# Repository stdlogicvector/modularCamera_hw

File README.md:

# ModularCamera Hardware

This repository contains the schematics and layouts for the PCBs that make up the ModularCamera system.
They are divided into three categories:

## Interface

This is the layer that connects the modularCamera to a PC. At the moment the following interfaces are implemented:

- USB3: Using a Cypress FX3 chip to communicate with a PC via an USB-C cable
- GigE: Providing a Gigabit Ethernet connection with an optional PoE add-on board

The boards are fully self contained, bringing all the power supplies and configuration memories they need.
To connect to the next layer, a 70 pin connector transports up to 42 signals plus 22x GND and 6x 5V.

## Processing

The central layer of the stack does everything from controlling the sensors,  processing the data and formatting it for output. Right now, there are two FPGA boards, but microcontrollers would also be possible.

- Spartan7: A XC72S15 FPGA from Xilinx
- Spartan6: A XC6SLX16 FPGA from Xilinx

Besides the FPGA, the boards have several power supplies for the FPGA, a configuration memory and a clock source. The connector to the next layer has  up to 42 signals plus 22x GND and 6x 5V.

## Sensor

This is were the modularity shines. With the high flexibility of the FPGAs, almost all sensors can be interfaced with minimal additional components.
The focus lies on image sensors, but the system isn't limited to processing pixels:

- AISC110C: A small image sensor with a resolution of 80x120 px but a maximum framerate of 40000fps! Configured via SPI.
- ADV7182: An SDTV Video Decoder that accepts lots of analog video formats. Configured via I2C.
- HallArray: An 8x8 array of hall sensors interfaced with an analog matrix. Makes magnetic fields visible.
- MT9P031: A 5MP B/W CMOS image sensor with 14fps. Configured via I2C.
- EV76C560: A 1.3MP B/W CMOS image sensor with global shutter and 60ps. Configured via SPI.
- LinearCCD: A board for interfacing several linear CCD arrays. Provides a driver chip for clocking&control signals, a step-up for power supply and up to 3 12bit 5MSPS ADCs. The sensors are connected via an additional board to accomodate for different pinouts.
- NOIP1SN300: A 1.3MP B/W CMOS image sensor with global shutter and up to 815fps. Configured via SPI.
- IBIS5-B-1300: A 1.3MP B/W CMOS image sensor with global shutter and 27fps. Configured via SPI. (WIP)
- Cameralink: A CameraLink-Base Interface with optional PoCL. Makes the modularCamera into a CameraLink framegrabber. (WIP)
- Microphone Array: A board containing three I2S MEMS microphones. (WIP)

The boards should provide everything necessary to operate the sensor. The connector to the lower layer provides 5V and the control/data interface.

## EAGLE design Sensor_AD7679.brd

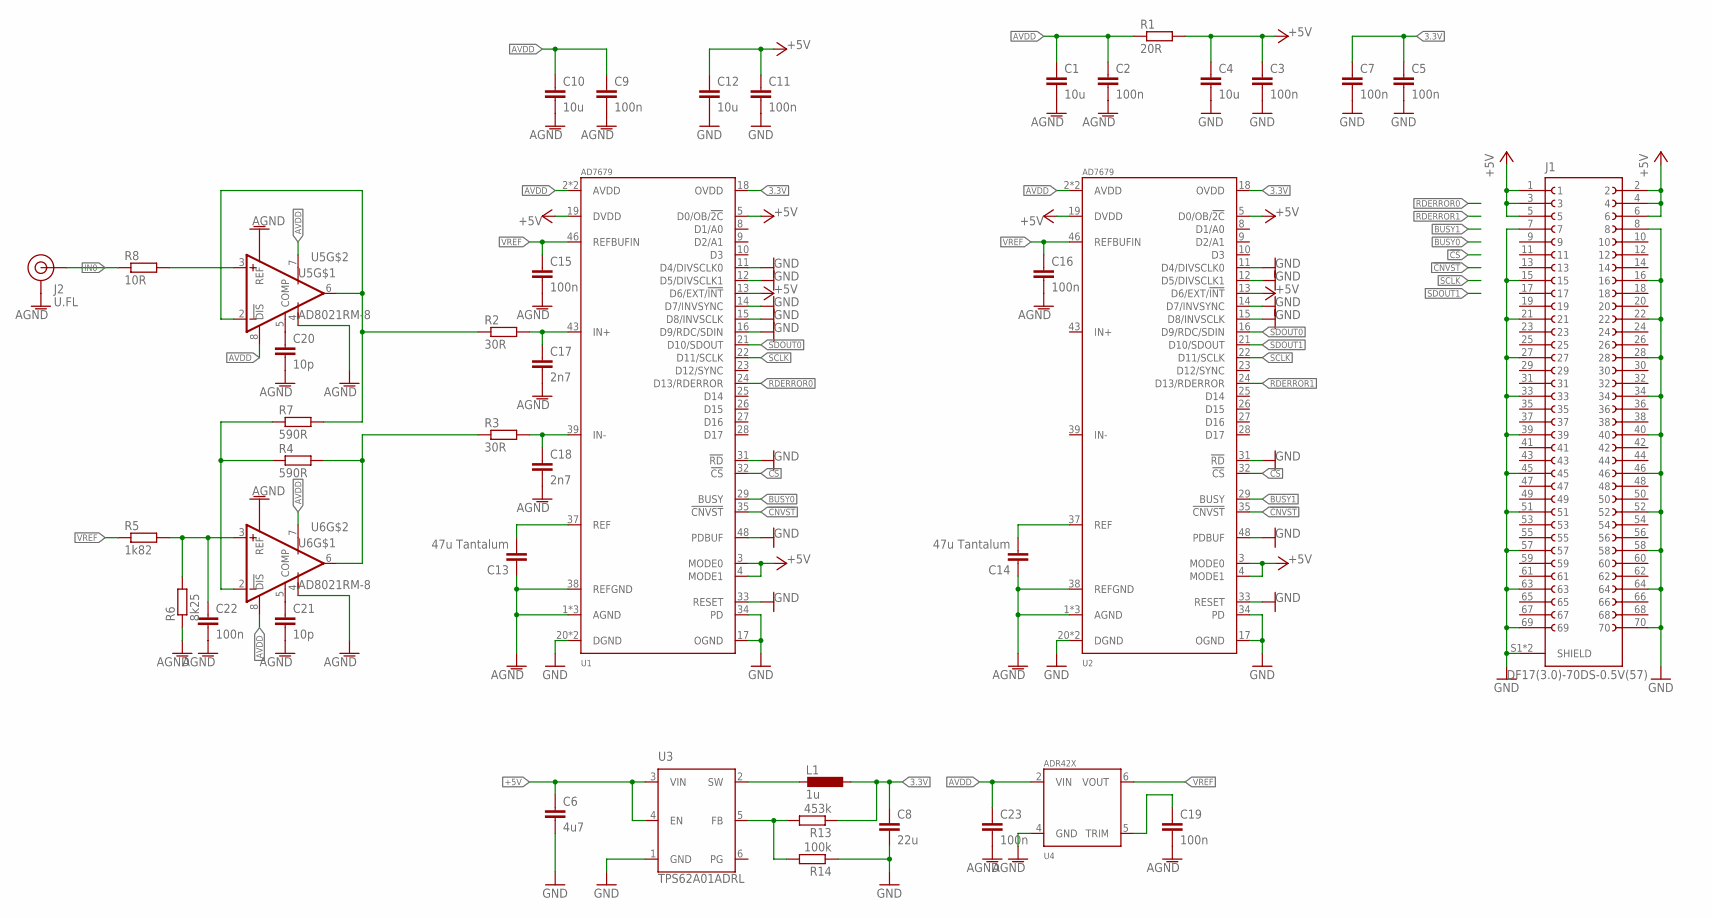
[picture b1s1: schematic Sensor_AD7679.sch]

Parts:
C1, C4, C10, C12: 10u; C0603
C2, C3, C5, C7, C9, C11, C15, C16, C19, C22, C23: 100n; C0402; LCSC C1525
C6: 4u7; C0603; LCSC C19666
C8: 22u; C0603; LCSC C109448
C13, C14: 47u Tantalum; C1206; DIGIKEY 478-TCA0J476M8R-02CT-ND
C17, C18: 2n7; C0402
C20, C21: 10p; C0402
J1: DF17(3.0)-70DS-0.5V(57)
J2: U.FL; DIGIKEY 26-U.FL-R-SMT-1(01)-ND
L1: 1u; L1008; MPN LQM2HPN1R0MG0L; DIGIKEY 490-5112-1-ND
R1: 20R; R0402
R2, R3: 30R; R0402
R4, R7: 590R; R0402
R5: 1k82; R0402
R6: 8k25; R0402
R8: 10R; R0402
R13: 453k; R0402; LCSC C137978
R14: 100k; R0402; DIGIKEY RMCF0402FT100KCT-ND
U1, U2: AD7679; LQFP48
U3: TPS62A01ADRL; SOTFL50P160X60-6N; DIGIKEY 296-TPS62A01ADRLRCT-ND
U4: ADR42X; MSOP08
U5, U6: AD8021RM-8; MSOP08

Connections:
3.3V: C5.1, C7.1, C8.1, L1.1, R13.1, U1.18 (OVDD), U2.18 (OVDD)
!CNVST: U1.35 (!CNVST), U2.35 (!CNVST)
!CS: U1.32 (!CS), U2.32 (!CS)
+5V: C3.1, C4.1, C6.1, C11.1, C12.1, J1.1, J1.2, J1.3, J1.4, J1.5, J1.6, R1.2, U1.3 (MODE0), U1.4 (MODE1), U1.5 (D0/OB/!2C), U1.19 (DVDD), U2.3 (MODE0), U2.4 (MODE1), U2.5 (D0/OB/!2C), U2.13 (D6/EXT/!INT), U2.19 (DVDD), U3.3 (VIN), U3.4 (EN)
AGND: C1.2, C2.2, C9.2, C10.2, C13.1, C14.1, C15.2, C16.2, C17.2, C18.2, C19.2, C20.2, C21.2, C22.2, C23.2, J2.1 (GND), J2.2 (GND), R6.1, U1.1 (AGND), U1.36 (AGND), U1.38 (REFGND), U1.44 (AGND), U2.1 (AGND), U2.36 (AGND), U2.38 (REFGND), U2.44 (AGND), U4.4 (GND), U5.1 (REF), U5.4 (V-), U6.1 (REF), U6.4 (V-)
AVDD: C1.1, C2.1, C9.1, C10.1, C23.1, R1.1, U1.2 (AVDD), U1.47 (AVDD), U2.2 (AVDD), U2.47 (AVDD), U4.2 (VIN), U5.7 (V+), U5.8 (!DIS), U6.7 (V+), U6.8 (!DIS)
BUSY0: U1.29 (BUSY)
BUSY1: U2.29 (BUSY)
GND: C3.2, C4.2, C5.2, C6.2, C7.2, C8.2, C11.2, C12.2, J1.7, J1.8, J1.15, J1.16, J1.21, J1.22, J1.27, J1.28, J1.33, J1.34, J1.39, J1.40, J1.45, J1.46, J1.51, J1.52, J1.57, J1.58, J1.63, J1.64, J1.69, J1.70, J1.S1 (SHIELD), J1.S2 (SHIELD), R14.1, U1.11 (D4/DIVSCLK0), U1.12 (D5/DIVSCLK1), U1.14 (D7/INVSYNC), U1.17 (OGND), U1.20 (DGND), U1.30 (DGND), U1.31 (!RD), U1.33 (RESET), U1.34 (PD), U1.48 (PDBUF), U2.11 (D4/DIVSCLK0), U2.12 (D5/DIVSCLK1), U2.14 (D7/INVSYNC), U2.15 (D8/INVSCLK), U2.17 (OGND), U2.20 (DGND), U2.30 (DGND), U2.31 (!RD), U2.33 (RESET), U2.34 (PD), U2.48 (PDBUF), U3.1 (GND)
IN0: J2.FEED (SIGNAL), R8.1
unnamed: C13.2, U1.37 (REF)
unnamed: C14.2, U2.37 (REF)
unnamed: U1.15 (D8/INVSCLK), U1.16 (D9/RDC/SDIN)
unnamed: R2.1, R7.2, U5.2 (-IN), U5.6 (OUT)
unnamed: C20.1, U5.5 (COMP)
unnamed: C17.1, R2.2, U1.43 (IN+)
unnamed: C18.1, R3.2, U1.39 (IN-)
unnamed: C19.1, U4.5 (TRIM)
unnamed: R4.1, R7.1, U6.2 (-IN)
unnamed: C21.1, U6.5 (COMP)
unnamed: R3.1, R4.2, U6.6 (OUT)
unnamed: C22.1, R5.2, R6.2, U6.3 (+IN)
unnamed: R8.2, U5.3 (+IN)
unnamed: R13.2, R14.2, U3.5 (FB)
unnamed: L1.2, U3.2 (SW)
RDERROR0: U1.24 (D13/RDERROR)
RDERROR1: U2.24 (D13/RDERROR)
SCLK: U1.22 (D11/SCLK), U2.22 (D11/SCLK)
SDOUT0: U1.21 (D10/SDOUT), U2.16 (D9/RDC/SDIN)
SDOUT1: U2.21 (D10/SDOUT)
VREF: C15.1, C16.1, R5.1, U1.46 (REFBUFIN), U2.46 (REFBUFIN), U4.6 (VOUT)

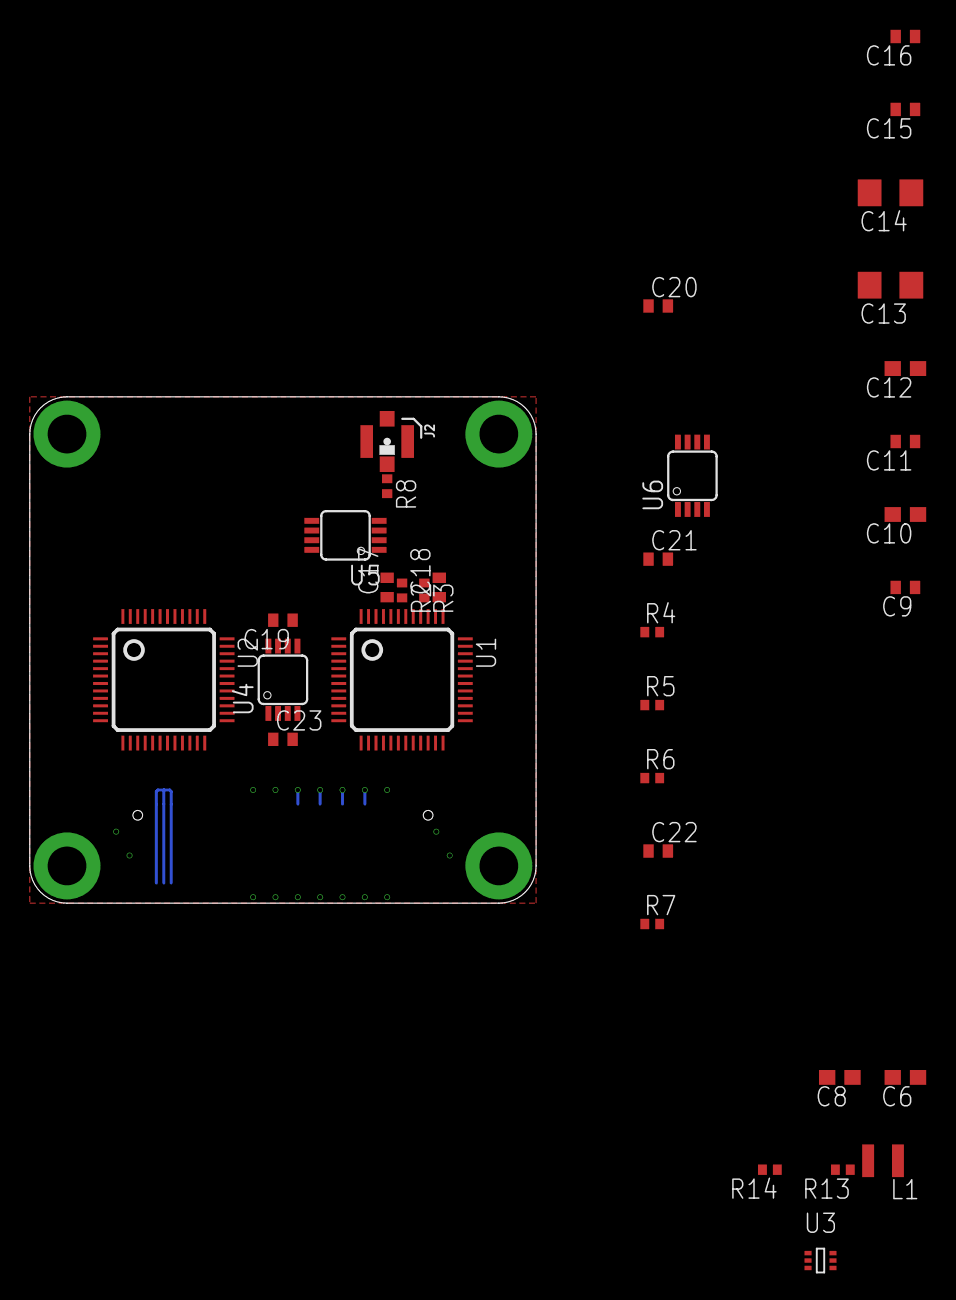
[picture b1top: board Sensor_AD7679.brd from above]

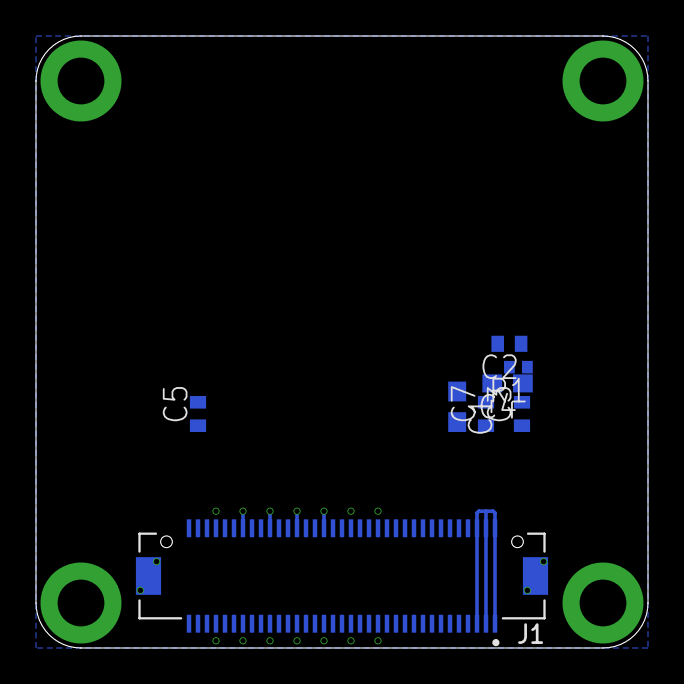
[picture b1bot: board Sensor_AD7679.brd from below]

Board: 4 copper layers, 34.0 x 34.0 mm, 42 parts (8 on the bottom side), 26 nets.

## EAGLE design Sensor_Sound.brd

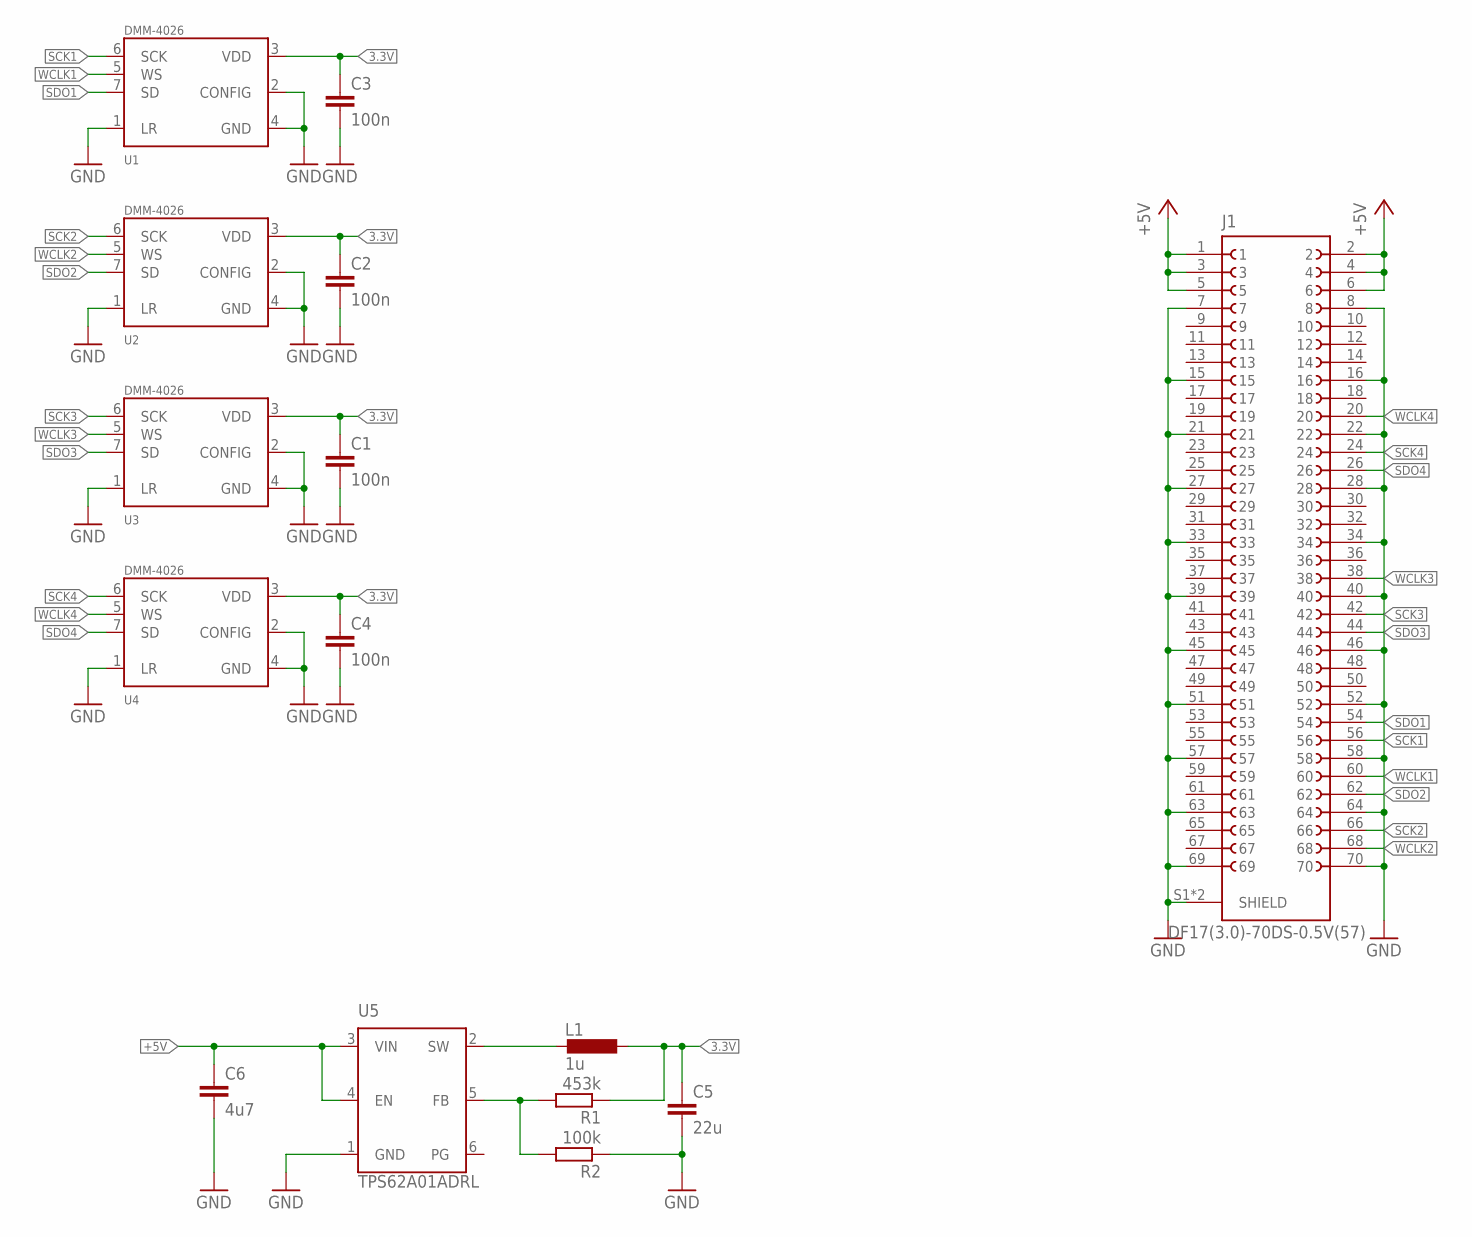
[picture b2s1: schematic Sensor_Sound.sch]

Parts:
C1, C2, C3, C4: 100n; C0402; LCSC C1525
C5: 22u; C0603; LCSC C109448
C6: 4u7; C0603; LCSC C19666
J1: DF17(3.0)-70DS-0.5V(57)
L1: 1u; L1008; MPN LQM2HPN1R0MG0L; DIGIKEY 490-5112-1-ND
R1: 453k; R0402; LCSC C137978
R2: 100k; R0402; DIGIKEY RMCF0402FT100KCT-ND
U1, U2, U3, U4: DMM-4026
U5: TPS62A01ADRL; SOTFL50P160X60-6N; DIGIKEY 296-TPS62A01ADRLRCT-ND

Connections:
3.3V: C1.1, C2.1, C3.1, C4.1, C5.1, L1.1, R1.1, U1.3 (VDD), U2.3 (VDD), U3.3 (VDD), U4.3 (VDD)
+5V: C6.1, J1.1, J1.2, J1.3, J1.4, J1.5, J1.6, U5.3 (VIN), U5.4 (EN)
GND: C1.2, C2.2, C3.2, C4.2, C5.2, C6.2, J1.7, J1.8, J1.15, J1.16, J1.21, J1.22, J1.27, J1.28, J1.33, J1.34, J1.39, J1.40, J1.45, J1.46, J1.51, J1.52, J1.57, J1.58, J1.63, J1.64, J1.69, J1.70, J1.S1 (SHIELD), J1.S2 (SHIELD), R2.1, U1.1 (LR), U1.2 (CONFIG), U1.4 (GND), U2.1 (LR), U2.2 (CONFIG), U2.4 (GND), U3.1 (LR), U3.2 (CONFIG), U3.4 (GND), U4.1 (LR), U4.2 (CONFIG), U4.4 (GND), U5.1 (GND)
unnamed: R1.2, R2.2, U5.5 (FB)
unnamed: L1.2, U5.2 (SW)
SCK1: J1.56, U1.6 (SCK)
SCK2: J1.66, U2.6 (SCK)
SCK3: J1.42, U3.6 (SCK)
SCK4: J1.24, U4.6 (SCK)
SDO1: J1.54, U1.7 (SD)
SDO2: J1.62, U2.7 (SD)
SDO3: J1.44, U3.7 (SD)
SDO4: J1.26, U4.7 (SD)
WCLK1: J1.60, U1.5 (WS)
WCLK2: J1.68, U2.5 (WS)
WCLK3: J1.38, U3.5 (WS)
WCLK4: J1.20, U4.5 (WS)

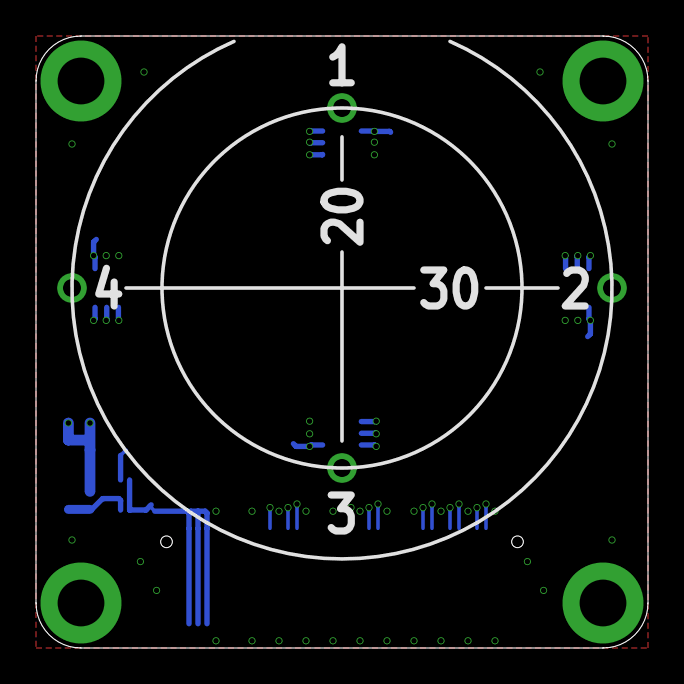
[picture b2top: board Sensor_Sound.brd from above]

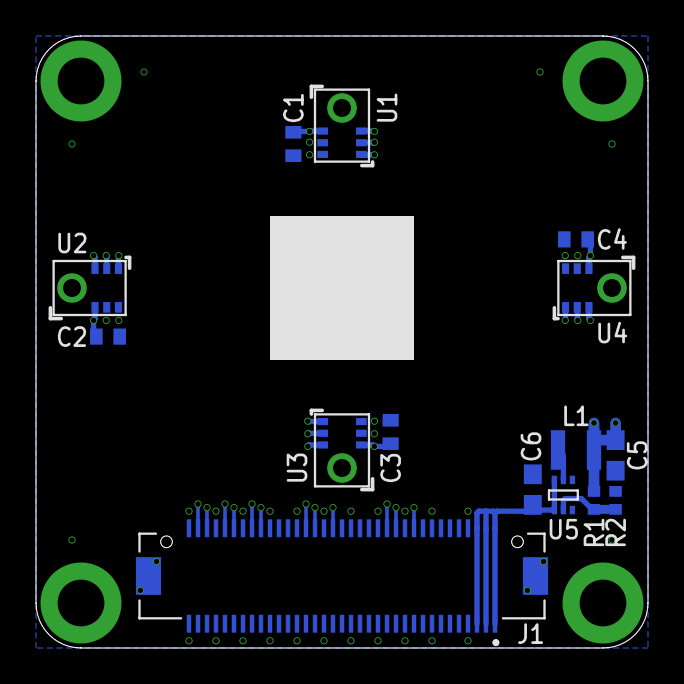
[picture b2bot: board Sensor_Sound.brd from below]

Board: 4 copper layers, 34.0 x 34.0 mm, 15 parts (15 on the bottom side), 17 nets.

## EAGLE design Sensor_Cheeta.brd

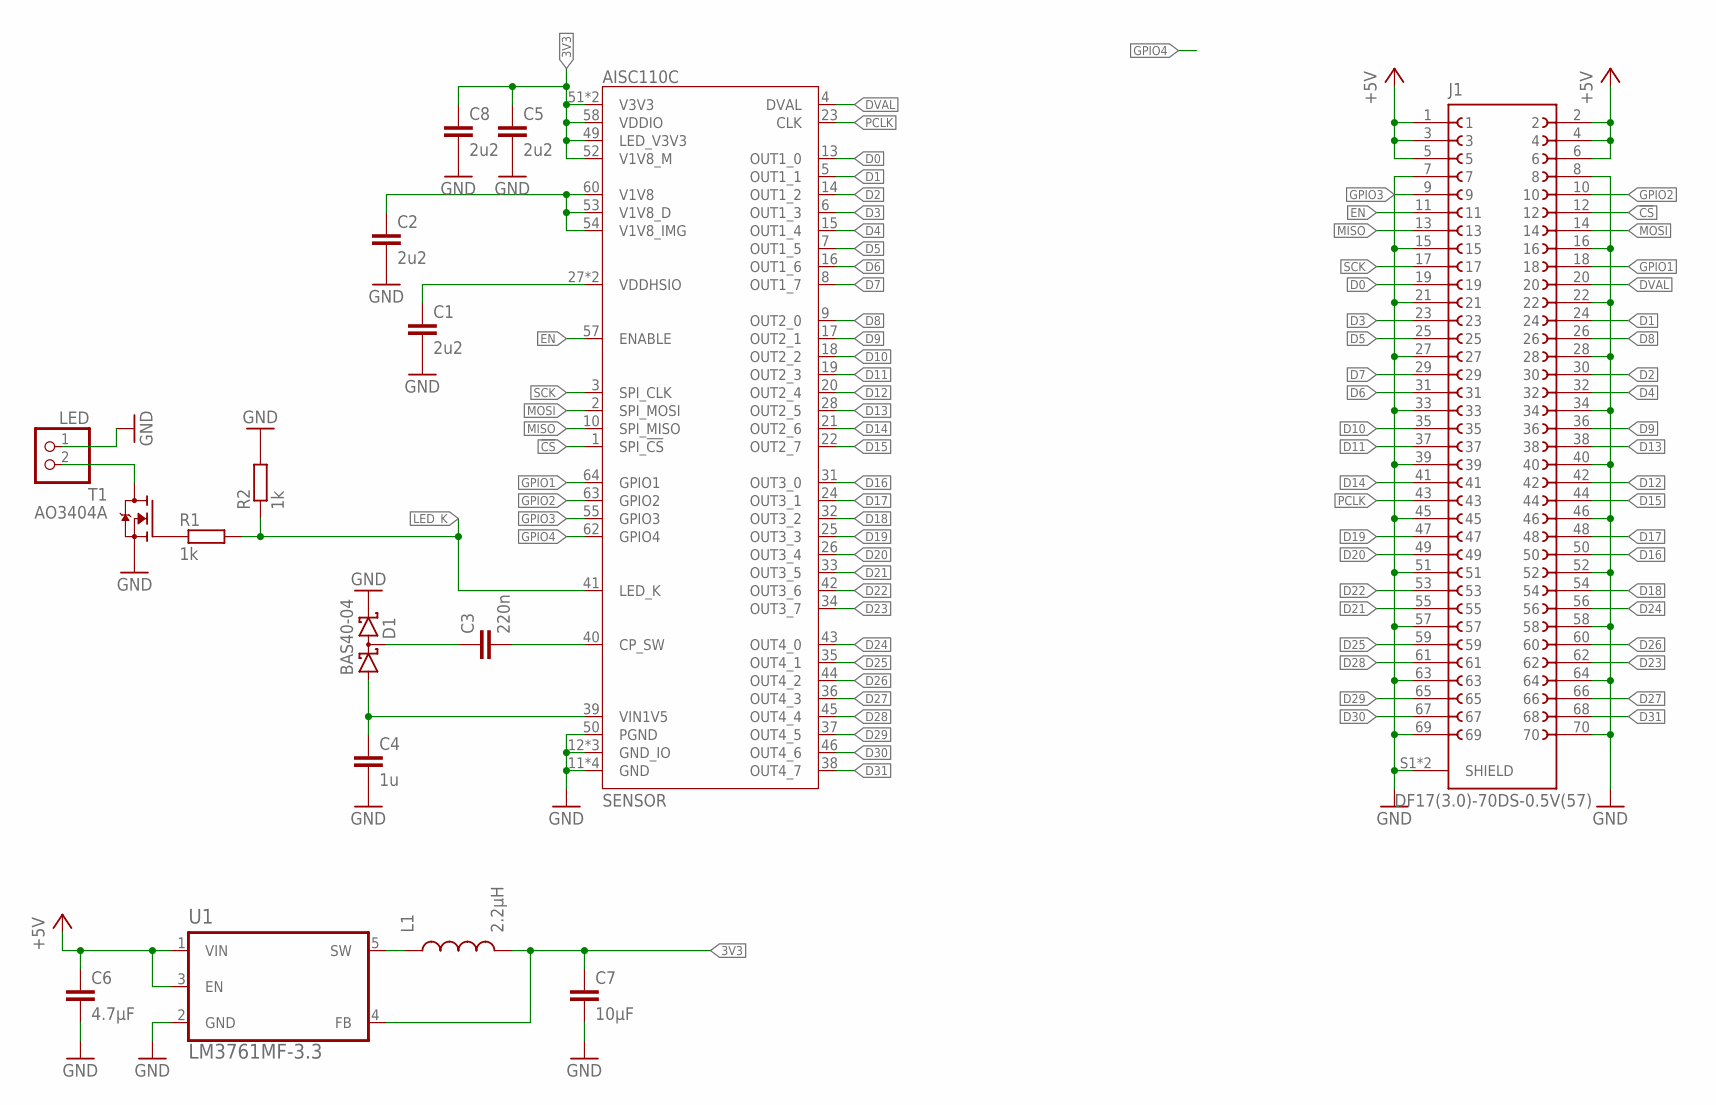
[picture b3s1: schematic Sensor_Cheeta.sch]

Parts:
C1, C2, C5, C8: 2u2; C0603
C3: 220n; C0603
C4: 1u; C0603
C6: 4.7µF; C0603
C7: 10µF; C0603
D1: BAS40-04; SOT23
J1: DF17(3.0)-70DS-0.5V(57)
L1: 2.2µH; SO3314; FARNELL 2457514
LED: PINHD-1X2; 1X02
R1, R2: 1k; R0603; LCSC C11702
SENSOR: AISC110C; 64_LD_OLGA
T1: AO3404A; SOT23; LCSC C30010
U1: LM3761MF-3.3; SOT95P284X122-5N

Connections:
3V3: C5.1, C7.1, C8.1, L1.2, SENSOR.49 (LED_V3V3), SENSOR.51 (V3V3), SENSOR.52 (V1V8_M), SENSOR.58 (VDDIO), SENSOR.59 (V3V3), U1.4 (FB)
!CS: J1.12, SENSOR.1 (SPI_!CS)
+5V: C6.1, J1.1, J1.2, J1.3, J1.4, J1.5, J1.6, U1.1 (VIN), U1.3 (EN)
D0: J1.19, SENSOR.13 (OUT1_0)
D1: J1.24, SENSOR.5 (OUT1_1)
D2: J1.30, SENSOR.14 (OUT1_2)
D3: J1.23, SENSOR.6 (OUT1_3)
D4: J1.32, SENSOR.15 (OUT1_4)
D5: J1.25, SENSOR.7 (OUT1_5)
D6: J1.31, SENSOR.16 (OUT1_6)
D7: J1.29, SENSOR.8 (OUT1_7)
D8: J1.26, SENSOR.9 (OUT2_0)
D9: J1.36, SENSOR.17 (OUT2_1)
D10: J1.35, SENSOR.18 (OUT2_2)
D11: J1.37, SENSOR.19 (OUT2_3)
D12: J1.42, SENSOR.20 (OUT2_4)
D13: J1.38, SENSOR.28 (OUT2_5)
D14: J1.41, SENSOR.21 (OUT2_6)
D15: J1.44, SENSOR.22 (OUT2_7)
D16: J1.50, SENSOR.31 (OUT3_0)
D17: J1.48, SENSOR.24 (OUT3_1)
D18: J1.54, SENSOR.32 (OUT3_2)
D19: J1.47, SENSOR.25 (OUT3_3)
D20: J1.49, SENSOR.26 (OUT3_4)
D21: J1.55, SENSOR.33 (OUT3_5)
D22: J1.53, SENSOR.42 (OUT3_6)
D23: J1.62, SENSOR.34 (OUT3_7)
D24: J1.56, SENSOR.43 (OUT4_0)
D25: J1.59, SENSOR.35 (OUT4_1)
D26: J1.60, SENSOR.44 (OUT4_2)
D27: J1.66, SENSOR.36 (OUT4_3)
D28: J1.61, SENSOR.45 (OUT4_4)
D29: J1.65, SENSOR.37 (OUT4_5)
D30: J1.67, SENSOR.46 (OUT4_6)
D31: J1.68, SENSOR.38 (OUT4_7)
DVAL: J1.20, SENSOR.4 (DVAL)
EN: J1.11, SENSOR.57 (ENABLE)
GND: C1.2, C2.2, C4.2, C5.2, C6.2, C7.2, C8.2, D1.2 (C2), J1.7, J1.8, J1.15, J1.16, J1.21, J1.22, J1.27, J1.28, J1.33, J1.34, J1.39, J1.40, J1.45, J1.46, J1.51, J1.52, J1.57, J1.58, J1.63, J1.64, J1.69, J1.70, J1.S1 (SHIELD), J1.S2 (SHIELD), LED.1, R2.2, SENSOR.11 (GND), SENSOR.12 (GND_IO), SENSOR.30 (GND_IO), SENSOR.47 (GND_IO), SENSOR.48 (GND), SENSOR.50 (PGND), SENSOR.56 (GND), SENSOR.61 (GND), T1.2 (S), U1.2 (GND)
GPIO1: J1.18, SENSOR.64 (GPIO1)
GPIO2: J1.10, SENSOR.63 (GPIO2)
GPIO3: J1.9, SENSOR.55 (GPIO3)
GPIO4: SENSOR.62 (GPIO4)
LED_K: R1.2, R2.1, SENSOR.41 (LED_K)
MISO: J1.13, SENSOR.10 (SPI_MISO)
MOSI: J1.14, SENSOR.2 (SPI_MOSI)
unnamed: C3.2, SENSOR.40 (CP_SW)
unnamed: C4.1, D1.1 (A1), SENSOR.39 (VIN1V5)
unnamed: C3.1, D1.3 (C1A2)
unnamed: LED.2, T1.3 (D)
unnamed: L1.1, U1.5 (SW)
unnamed: C2.1, SENSOR.53 (V1V8_D), SENSOR.54 (V1V8_IMG), SENSOR.60 (V1V8)
unnamed: C1.1, SENSOR.27 (VDDHSIO), SENSOR.29 (VDDHSIO)
unnamed: R1.1, T1.1 (G)
PCLK: J1.43, SENSOR.23 (CLK)
SCK: J1.17, SENSOR.3 (SPI_CLK)

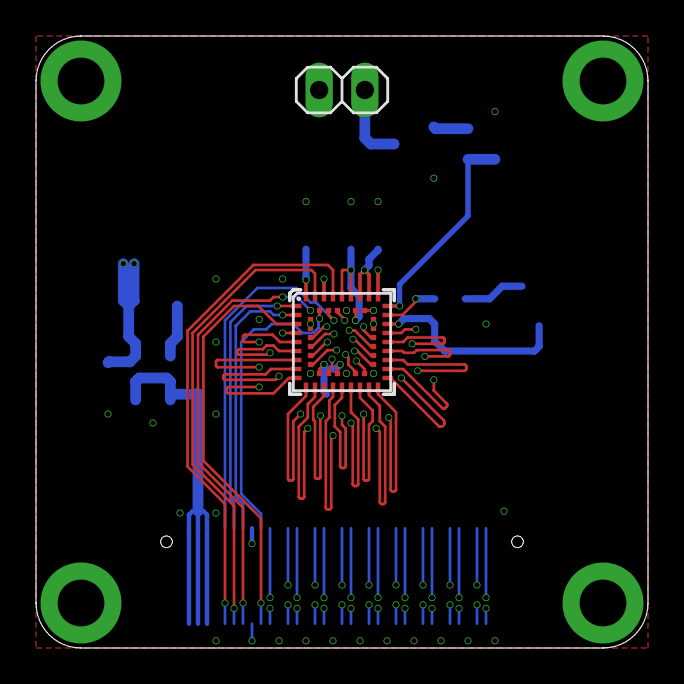
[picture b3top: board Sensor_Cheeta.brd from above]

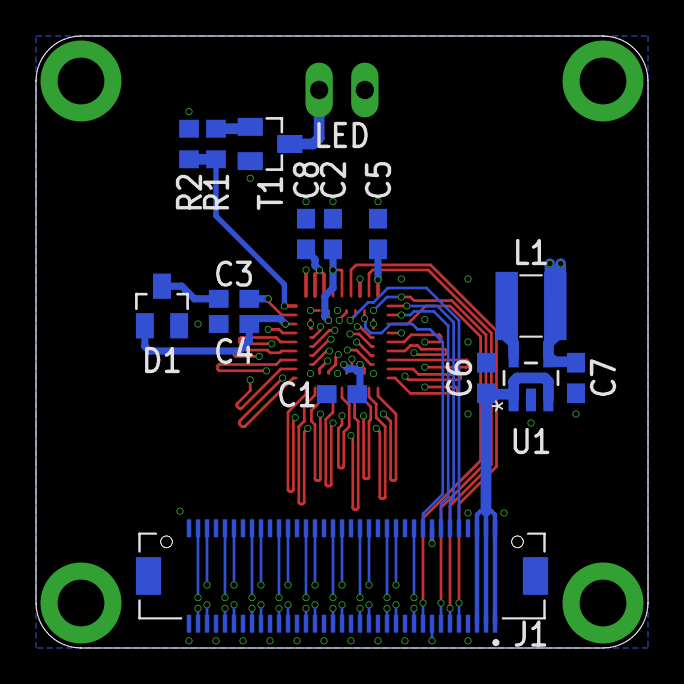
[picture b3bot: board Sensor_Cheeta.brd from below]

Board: 4 copper layers, 34.0 x 34.0 mm, 17 parts (15 on the bottom side), 54 nets.

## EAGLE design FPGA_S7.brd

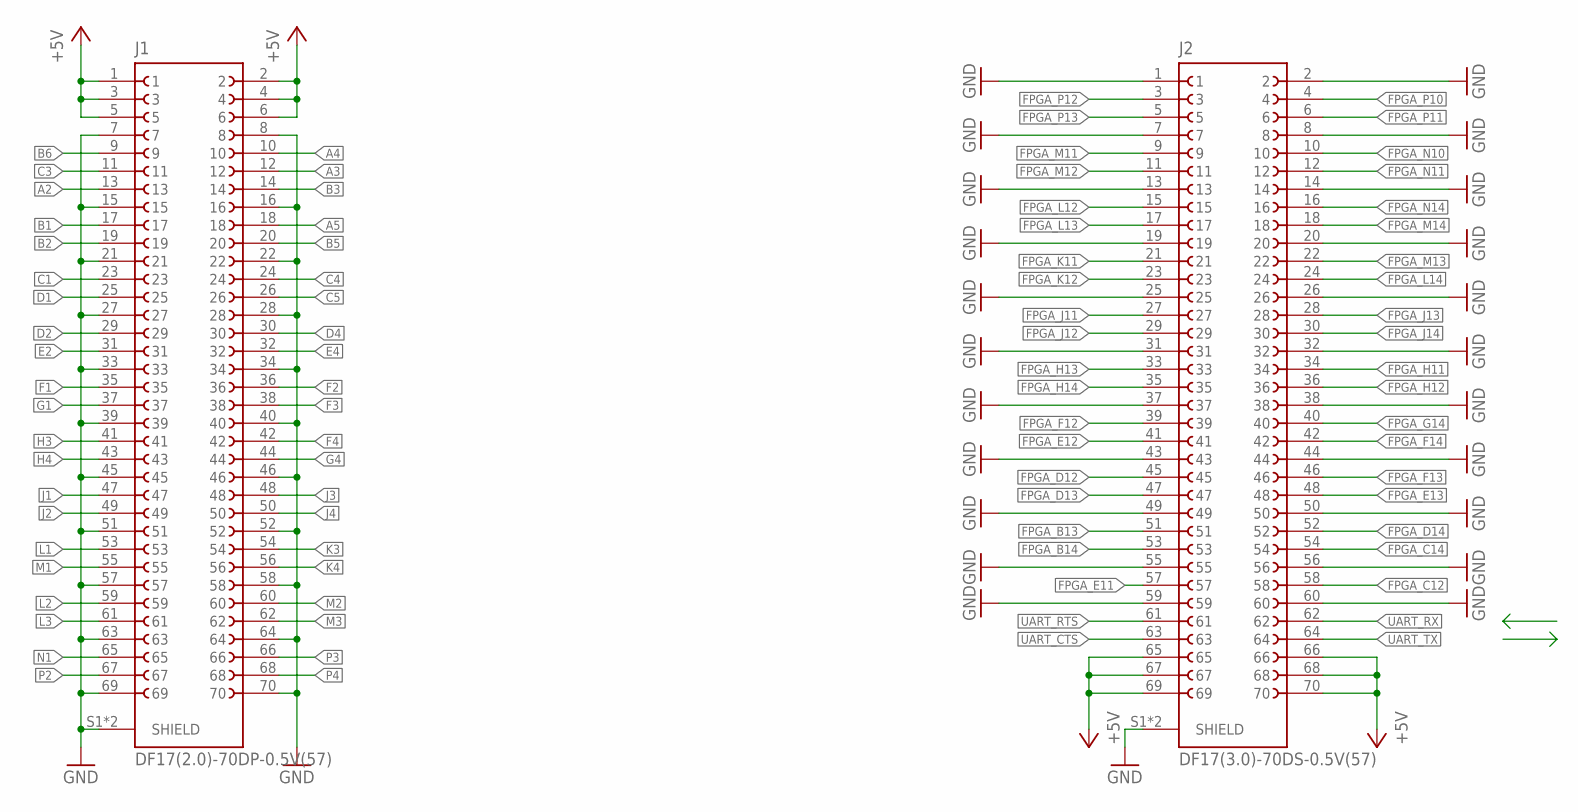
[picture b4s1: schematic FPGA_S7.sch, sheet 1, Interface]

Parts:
J1: DF17(2.0)-70DP-0.5V(57); DIGIKEY H11133CT-ND
J2: DF17(3.0)-70DS-0.5V(57); DIGIKEY H11112CT-ND

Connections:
+5V: J1.1, J1.2, J1.3, J1.4, J1.5, J1.6, J2.65, J2.66, J2.67, J2.68, J2.69, J2.70; also elsewhere on the board
A2: J1.13; also elsewhere on the board
A3: J1.12; also elsewhere on the board
A4: J1.10; also elsewhere on the board
A5: J1.18; also elsewhere on the board
B1: J1.17; also elsewhere on the board
B2: J1.19; also elsewhere on the board
B3: J1.14; also elsewhere on the board
B5: J1.20; also elsewhere on the board
B6: J1.9; also elsewhere on the board
C1: J1.23; also elsewhere on the board
C3: J1.11; also elsewhere on the board
C4: J1.24; also elsewhere on the board
C5: J1.26; also elsewhere on the board
D1: J1.25; also elsewhere on the board
D2: J1.29; also elsewhere on the board
D4: J1.30; also elsewhere on the board
E2: J1.31; also elsewhere on the board
E4: J1.32; also elsewhere on the board
F1: J1.35; also elsewhere on the board
F2: J1.36; also elsewhere on the board
F3: J1.38; also elsewhere on the board
F4: J1.42; also elsewhere on the board
FPGA_B13: J2.51; also elsewhere on the board
FPGA_B14: J2.53; also elsewhere on the board
FPGA_C12: J2.58; also elsewhere on the board
FPGA_C14: J2.54; also elsewhere on the board
FPGA_D12: J2.45; also elsewhere on the board
FPGA_D13: J2.47; also elsewhere on the board
FPGA_D14: J2.52; also elsewhere on the board
FPGA_E11: J2.57; also elsewhere on the board
FPGA_E12: J2.41; also elsewhere on the board
FPGA_E13: J2.48; also elsewhere on the board
FPGA_F12: J2.39; also elsewhere on the board
FPGA_F13: J2.46; also elsewhere on the board
FPGA_F14: J2.42; also elsewhere on the board
FPGA_G14: J2.40; also elsewhere on the board
FPGA_H11: J2.34; also elsewhere on the board
FPGA_H12: J2.36; also elsewhere on the board
FPGA_H13: J2.33; also elsewhere on the board
FPGA_H14: J2.35; also elsewhere on the board
FPGA_J11: J2.27; also elsewhere on the board
FPGA_J12: J2.29; also elsewhere on the board
FPGA_J13: J2.28; also elsewhere on the board
FPGA_J14: J2.30; also elsewhere on the board
FPGA_K11: J2.21; also elsewhere on the board
FPGA_K12: J2.23; also elsewhere on the board
FPGA_L12: J2.15; also elsewhere on the board
FPGA_L13: J2.17; also elsewhere on the board
FPGA_L14: J2.24; also elsewhere on the board
FPGA_M11: J2.9; also elsewhere on the board
FPGA_M12: J2.11; also elsewhere on the board
FPGA_M13: J2.22; also elsewhere on the board
FPGA_M14: J2.18; also elsewhere on the board
FPGA_N10: J2.10; also elsewhere on the board
FPGA_N11: J2.12; also elsewhere on the board
FPGA_N14: J2.16; also elsewhere on the board
FPGA_P10: J2.4; also elsewhere on the board
FPGA_P11: J2.6; also elsewhere on the board
FPGA_P12: J2.3; also elsewhere on the board
FPGA_P13: J2.5; also elsewhere on the board
G1: J1.37; also elsewhere on the board
G4: J1.44; also elsewhere on the board
GND: J1.7, J1.8, J1.15, J1.16, J1.21, J1.22, J1.27, J1.28, J1.33, J1.34, J1.39, J1.40, J1.45, J1.46, J1.51, J1.52, J1.57, J1.58, J1.63, J1.64, J1.69, J1.70, J1.S1 (SHIELD), J1.S2 (SHIELD), J2.1, J2.2, J2.7, J2.8, J2.13, J2.14, J2.19, J2.20, J2.25, J2.26, J2.31, J2.32, J2.37, J2.38, J2.43, J2.44, J2.49, J2.50, J2.55, J2.56, J2.59, J2.60, J2.S1 (SHIELD), J2.S2 (SHIELD); also elsewhere on the board
H3: J1.41; also elsewhere on the board
H4: J1.43; also elsewhere on the board
J1: J1.47; also elsewhere on the board
J2: J1.49; also elsewhere on the board
J3: J1.48; also elsewhere on the board
J4: J1.50; also elsewhere on the board
K3: J1.54; also elsewhere on the board
K4: J1.56; also elsewhere on the board
L1: J1.53; also elsewhere on the board
L2: J1.59; also elsewhere on the board
L3: J1.61; also elsewhere on the board
M1: J1.55; also elsewhere on the board
M2: J1.60; also elsewhere on the board
M3: J1.62; also elsewhere on the board
N1: J1.65; also elsewhere on the board
P2: J1.67; also elsewhere on the board
P3: J1.66; also elsewhere on the board
P4: J1.68; also elsewhere on the board
UART_CTS: J2.63; also elsewhere on the board
UART_RTS: J2.61; also elsewhere on the board
UART_RX: J2.62; also elsewhere on the board
UART_TX: J2.64; also elsewhere on the board

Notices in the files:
parts and their libraries:
SparkFun-Connectors: Licensing: Creative Commons ShareAlike 4.0 International - https://creativecommons.org/licenses/by-sa/4.0
onsemi: COPYRIGHT: Copyright (C) 2025 Ultra Librarian. All rights reserved.
crystal-geyer_V1_0: Copyright: Geyer-Electronic
